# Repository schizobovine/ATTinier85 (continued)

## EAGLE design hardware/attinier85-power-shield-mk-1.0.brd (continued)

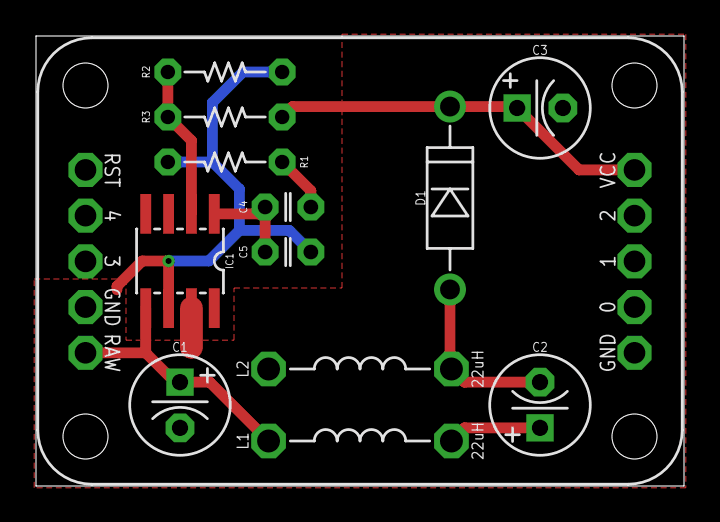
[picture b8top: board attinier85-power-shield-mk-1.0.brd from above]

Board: 2 copper layers, 36.0 x 25.0 mm, 14 parts (0 on the bottom side), 8 nets.

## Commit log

2015-05-03 rename all the things
2015-05-03 renaming parts
2015-05-03 more renaming
2015-05-03 cleaning up version spoo
2015-05-03 shedding useless version
2015-05-03 touchup
2015-05-07 wooo
2015-05-09 smd based mobo for '85
2015-05-11 new PTH version to match ATTinier84 form factor
2017-05-31 more boards
2017-06-01 alskdf
